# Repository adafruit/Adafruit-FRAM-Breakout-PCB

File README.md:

# Adafruit FRAM Breakout PCBs

&nbsp; <br />
Click to purchase from the Adafruit Shop:
- [I2C Version](https://www.adafruit.com/product/1895)
- [SPI Version](https://www.adafruit.com/product/1897)
- [2 Mbit SPI Version](https://www.adafruit.com/product/4718)
- [4 Mbit SPI Version](https://www.adafruit.com/product/4719)

FRAM, or Ferroelectric Ram, is pretty cool! It's similar to Dynamic random-access memory, only with a ferroelectric layer instead of a dielectric layer. This gives it stable handling (the bytes you write are non-volatile) with dynamic responsiveness (you can write them very fast!)

Now, with our FRAM breakout boards, you can add some FRAM storage to your next DIY project. FRAM allows for a lower power usage and a faster write performance. It's excellent for low-power or inconsistent-power datalogging or data buffering where you want to stream data fast while also keeping the data when there's no power. Unlike Flash or EEPROM there's no pages to worry about. Each byte can be read/written 10,000,000,000,000 times so you don't have to worry too much about wear leveling.

These particular FRAM chips have 64 Kbits (8 KBytes) of storage, interfaces using SPI or I2C (select the correct board for the correct bus, they cannot do both!), and can run at up to 20MHz SPI clock rates. Each byte can be read and written instantaneously (like SRAM) but will keep the memory for 95 years at room temperature.

PCB files for Adafruit I2C &amp; SPI FRAM Breakout Boards. 
Format is EagleCAD schematic and board layout

For more details, check out the product pages at

-----> https://www.adafruit.com/products/1895

-----> https://www.adafruit.com/products/1897

### License

Adafruit invests time and resources providing this open source design, please support Adafruit and open-source hardware by purchasing products from [Adafruit](https://www.adafruit.com)!

All text above must be included in any redistribution

Designed by Limor Fried/Ladyada for Adafruit Industries.
Creative Commons Attribution/Share-Alike, all text above must be included in any redistribution. 
See license.txt for additional information.

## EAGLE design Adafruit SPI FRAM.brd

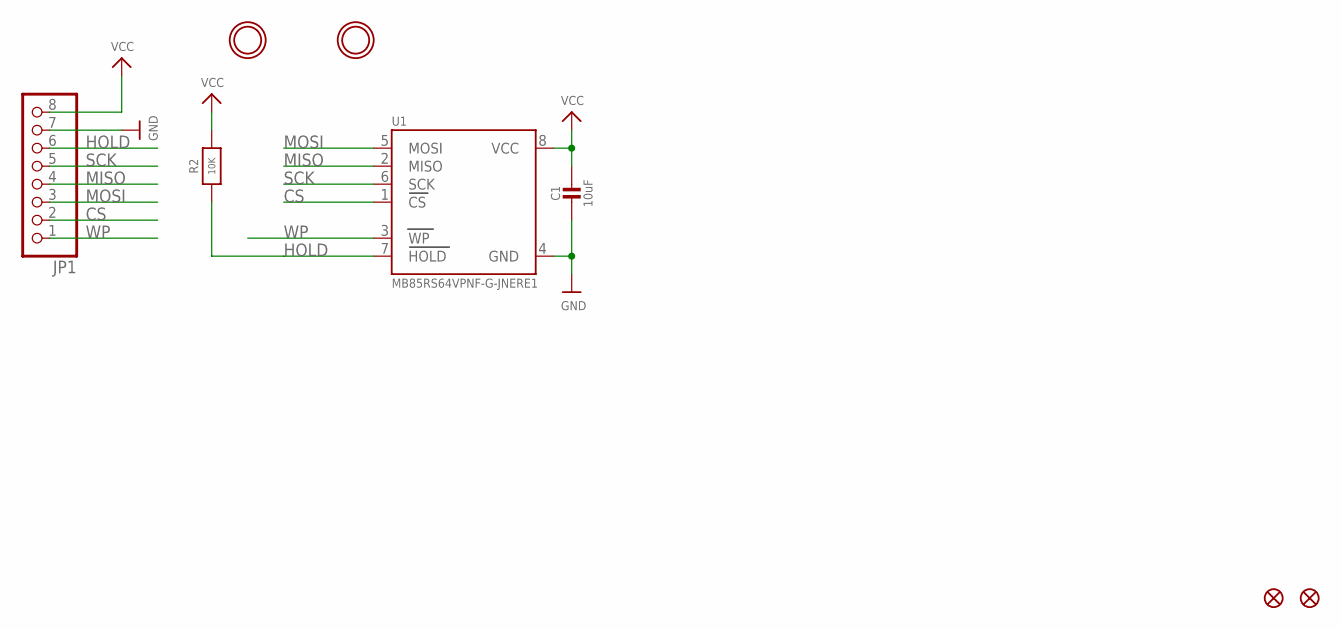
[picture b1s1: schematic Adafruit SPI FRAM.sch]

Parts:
C1: 10uF; _0805MP
FID1, FID2: FIDUCIAL""; FIDUCIAL_1MM
JP1: HEADER-1X870MIL; 1X08_ROUND_70
R2: 10K; _0805MP
U1: MB85RS64VPNF-G-JNERE1; SOIC8_150MIL
U$5, U$6: MOUNTINGHOLE2.5; MOUNTINGHOLE_2.5_PLATED

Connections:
CS: JP1.2, U1.1 (CS)
GND: C1.2, JP1.7, U1.4 (GND)
HOLD: JP1.6, R2.1, U1.7 (HOLD)
MISO: JP1.4, U1.2 (MISO)
MOSI: JP1.3, U1.5 (MOSI)
SCK: JP1.5, U1.6 (SCK)
VCC: C1.1, JP1.8, R2.2, U1.8 (VCC)
WP: JP1.1, U1.3 (WP)

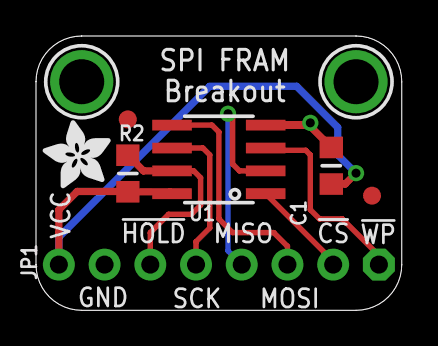
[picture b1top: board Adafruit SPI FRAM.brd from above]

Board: 2 copper layers, 20.3 x 15.2 mm, 10 parts (1 on the bottom side), 8 nets.

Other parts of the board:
U$4, U$7: ADAFRUIT_3.5MM

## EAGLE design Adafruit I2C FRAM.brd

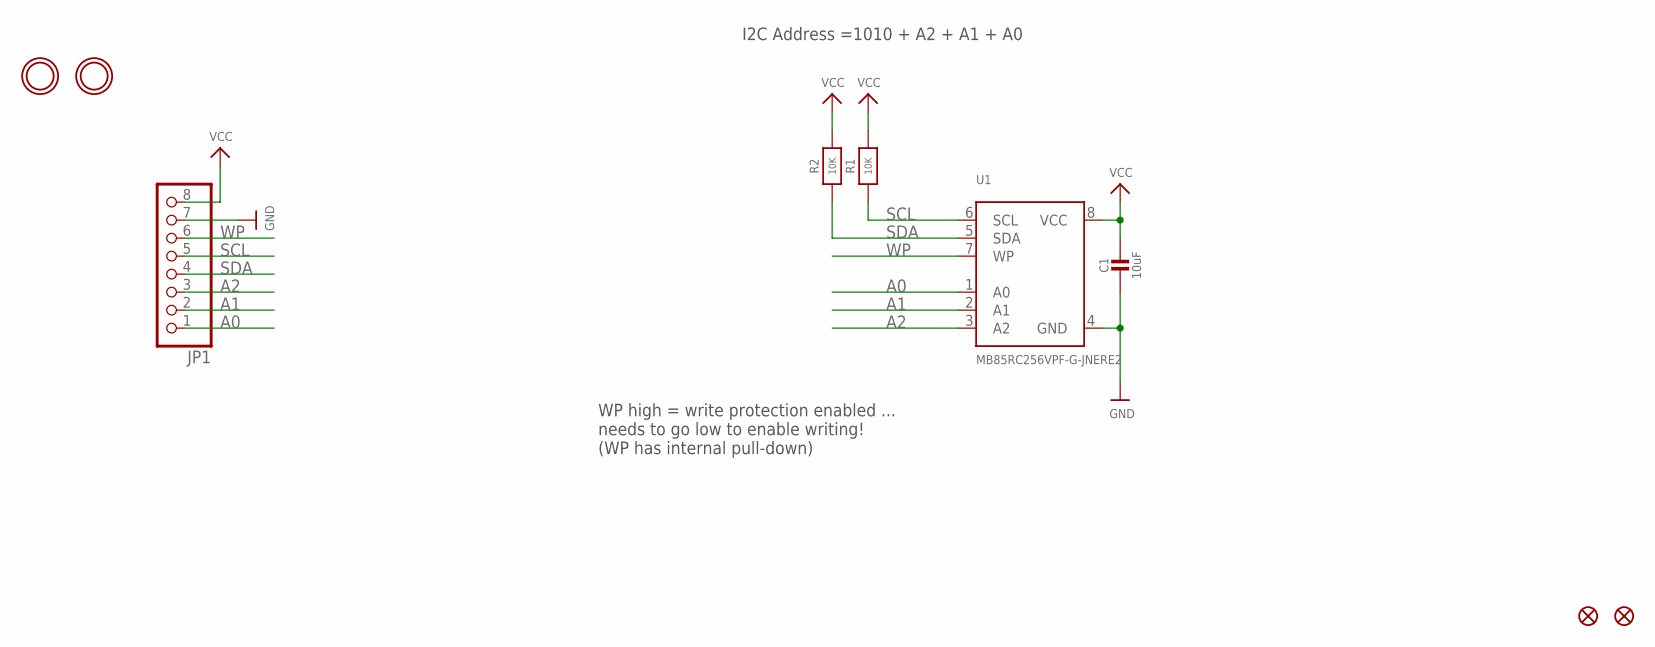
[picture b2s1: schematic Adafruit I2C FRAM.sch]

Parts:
C1: 10uF; _0805MP
FID1, FID2: FIDUCIAL""; FIDUCIAL_1MM
JP1: HEADER-1X870MIL; 1X08_ROUND_70
R1, R2: 10K; _0805MP
U1: MB85RC256VPF-G-JNERE2; SOIC8_208MIL
U$5, U$6: MOUNTINGHOLE2.5; MOUNTINGHOLE_2.5_PLATED

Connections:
A0: JP1.1, U1.1 (A0)
A1: JP1.2, U1.2 (A1)
A2: JP1.3, U1.3 (A2)
GND: C1.2, JP1.7, U1.4 (GND)
SCL: JP1.5, R1.1, U1.6 (SCL)
SDA: JP1.4, R2.1, U1.5 (SDA)
VCC: C1.1, JP1.8, R1.2, R2.2, U1.8 (VCC)
WP: JP1.6, U1.7 (WP)

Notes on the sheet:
WP high = write protection enabled ... needs to go low to enable writing! (WP has internal pull-down)
I2C Address =1010 + A2 + A1 + A0

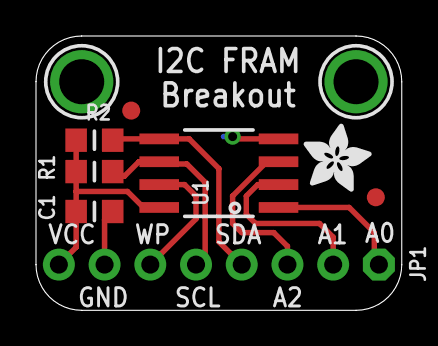
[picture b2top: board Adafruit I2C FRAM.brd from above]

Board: 2 copper layers, 20.3 x 15.2 mm, 10 parts (0 on the bottom side), 8 nets.

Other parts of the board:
U$4: ADAFRUIT_3.5MM

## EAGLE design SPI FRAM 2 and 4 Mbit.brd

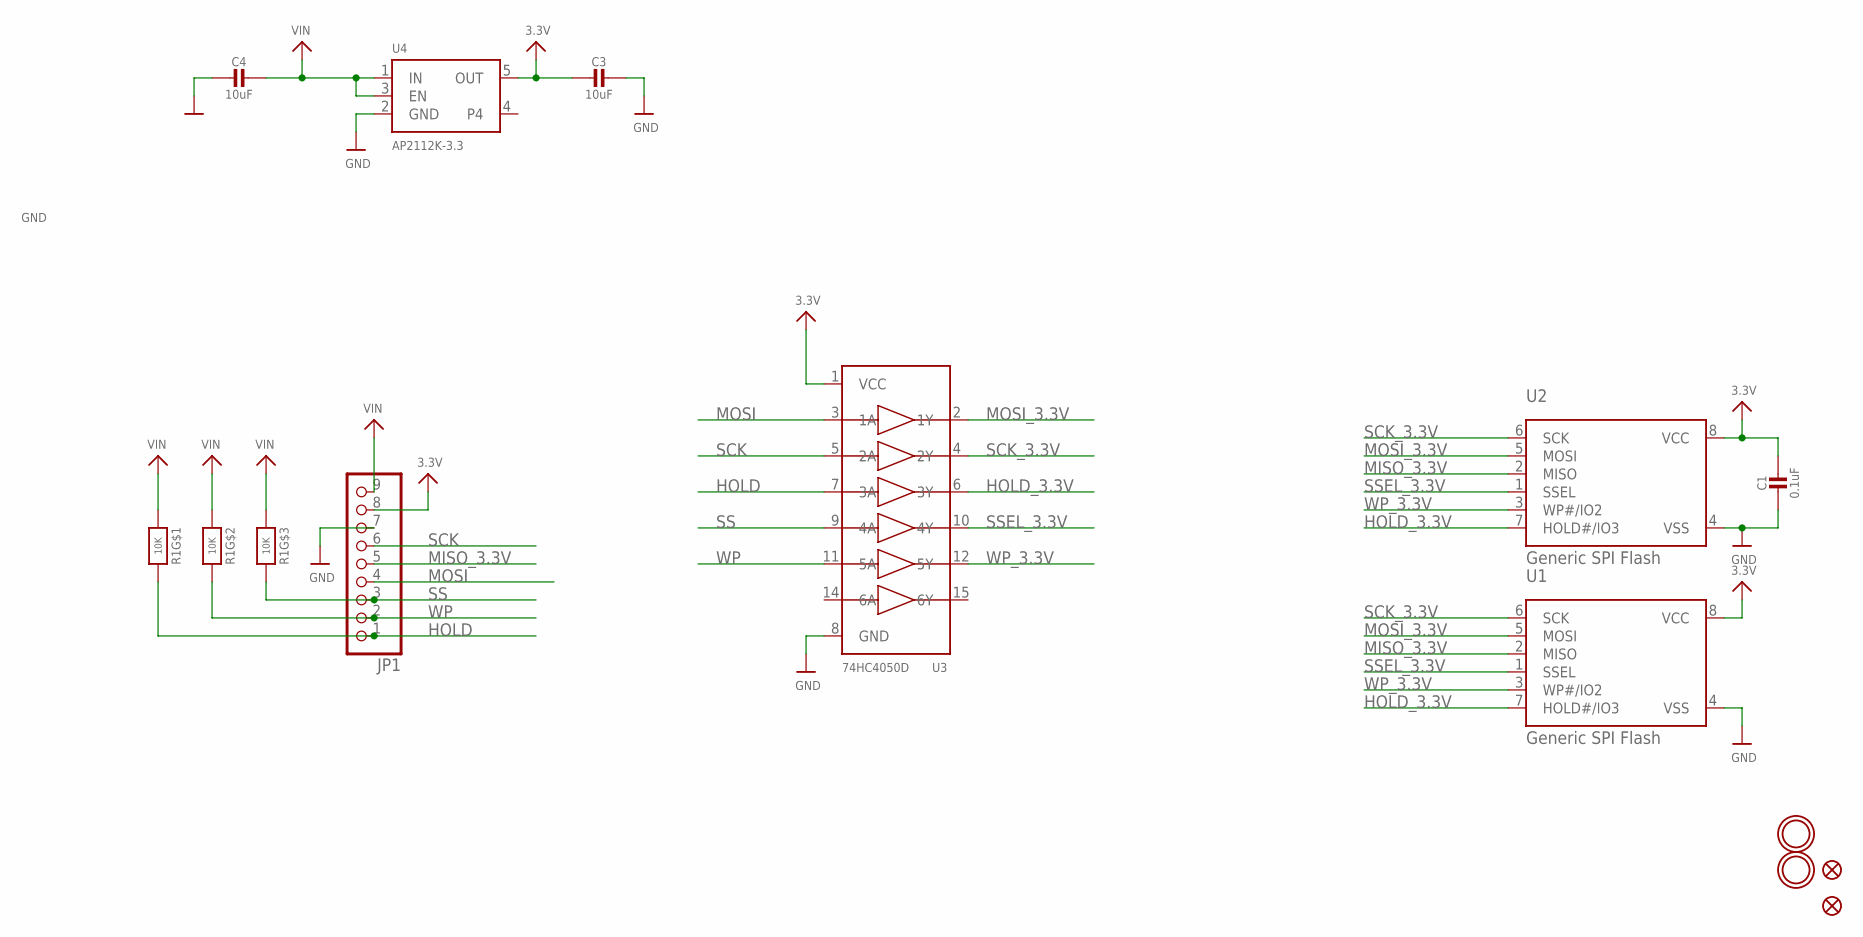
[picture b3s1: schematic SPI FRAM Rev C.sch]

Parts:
C1: 0.1uF; 0603-NO
C3, C4: 10uF; 0805-NO
FID2, FID3: FIDUCIAL_1MM
JP1: HEADER-1X970MIL; 1X09_ROUND_70
R1: 10K; RESPACK_4X0603
U1: Generic SPI Flash; SOIC8_208MIL
U2: Generic SPI Flash; USON8
U3: 74HC4050D; TSSOP16
U4: AP2112K-3.3; SOT23-5
U$16, U$17: MOUNTINGHOLE2.5; MOUNTINGHOLE_2.5_PLATED

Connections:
3.3V: C1.1, C3.2, JP1.8, U1.8 (VCC), U2.8 (VCC), U3.1 (VCC), U4.5 (OUT)
GND: C1.2, C3.1, C4.2, JP1.7, U1.4 (VSS), U2.4 (VSS), U3.8 (GND), U4.2 (GND)
HOLD: JP1.1, R1.8 (2), U3.7 (3A)
HOLD_3.3V: U1.7 (HOLD#/IO3), U2.7 (HOLD#/IO3), U3.6 (3Y)
MISO_3.3V: JP1.5, U1.2 (MISO), U2.2 (MISO)
MOSI: JP1.4, U3.3 (1A)
MOSI_3.3V: U1.5 (MOSI), U2.5 (MOSI), U3.2 (1Y)
SCK: JP1.6, U3.5 (2A)
SCK_3.3V: U1.6 (SCK), U2.6 (SCK), U3.4 (2Y)
SS: JP1.3, R1.6 (2), U3.9 (4A)
SSEL_3.3V: U1.1 (SSEL), U2.1 (SSEL), U3.10 (4Y)
VIN: C4.1, JP1.9, R1.1, R1.2 (1), R1.3 (1), U4.1 (IN), U4.3 (EN)
WP: JP1.2, R1.7 (2), U3.11 (5A)
WP_3.3V: U1.3 (WP#/IO2), U2.3 (WP#/IO2), U3.12 (5Y)

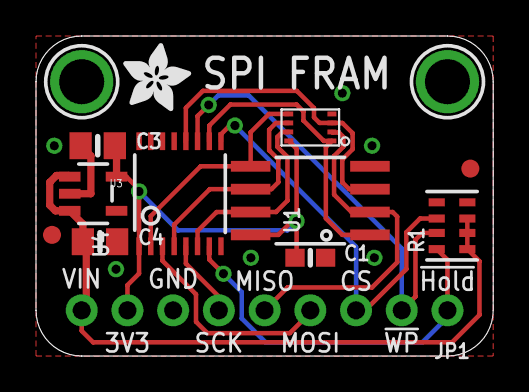
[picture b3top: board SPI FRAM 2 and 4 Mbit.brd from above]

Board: 2 copper layers, 25.4 x 17.8 mm, 15 parts (1 on the bottom side), 14 nets.

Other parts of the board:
U$19: ADAFRUIT_3.5MM
U$21: PCBFEAT-REV-040

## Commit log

2015-01-14 save a repo - double up!
2020-09-03 Added files for pid 4718
2020-09-04 Renamed files for 4718 and 4719, added them to README

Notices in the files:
parts and their libraries:
microbuilder: This work is placed in the public domain, and may be freely used for commercial and non-commercial work with the following conditions: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
